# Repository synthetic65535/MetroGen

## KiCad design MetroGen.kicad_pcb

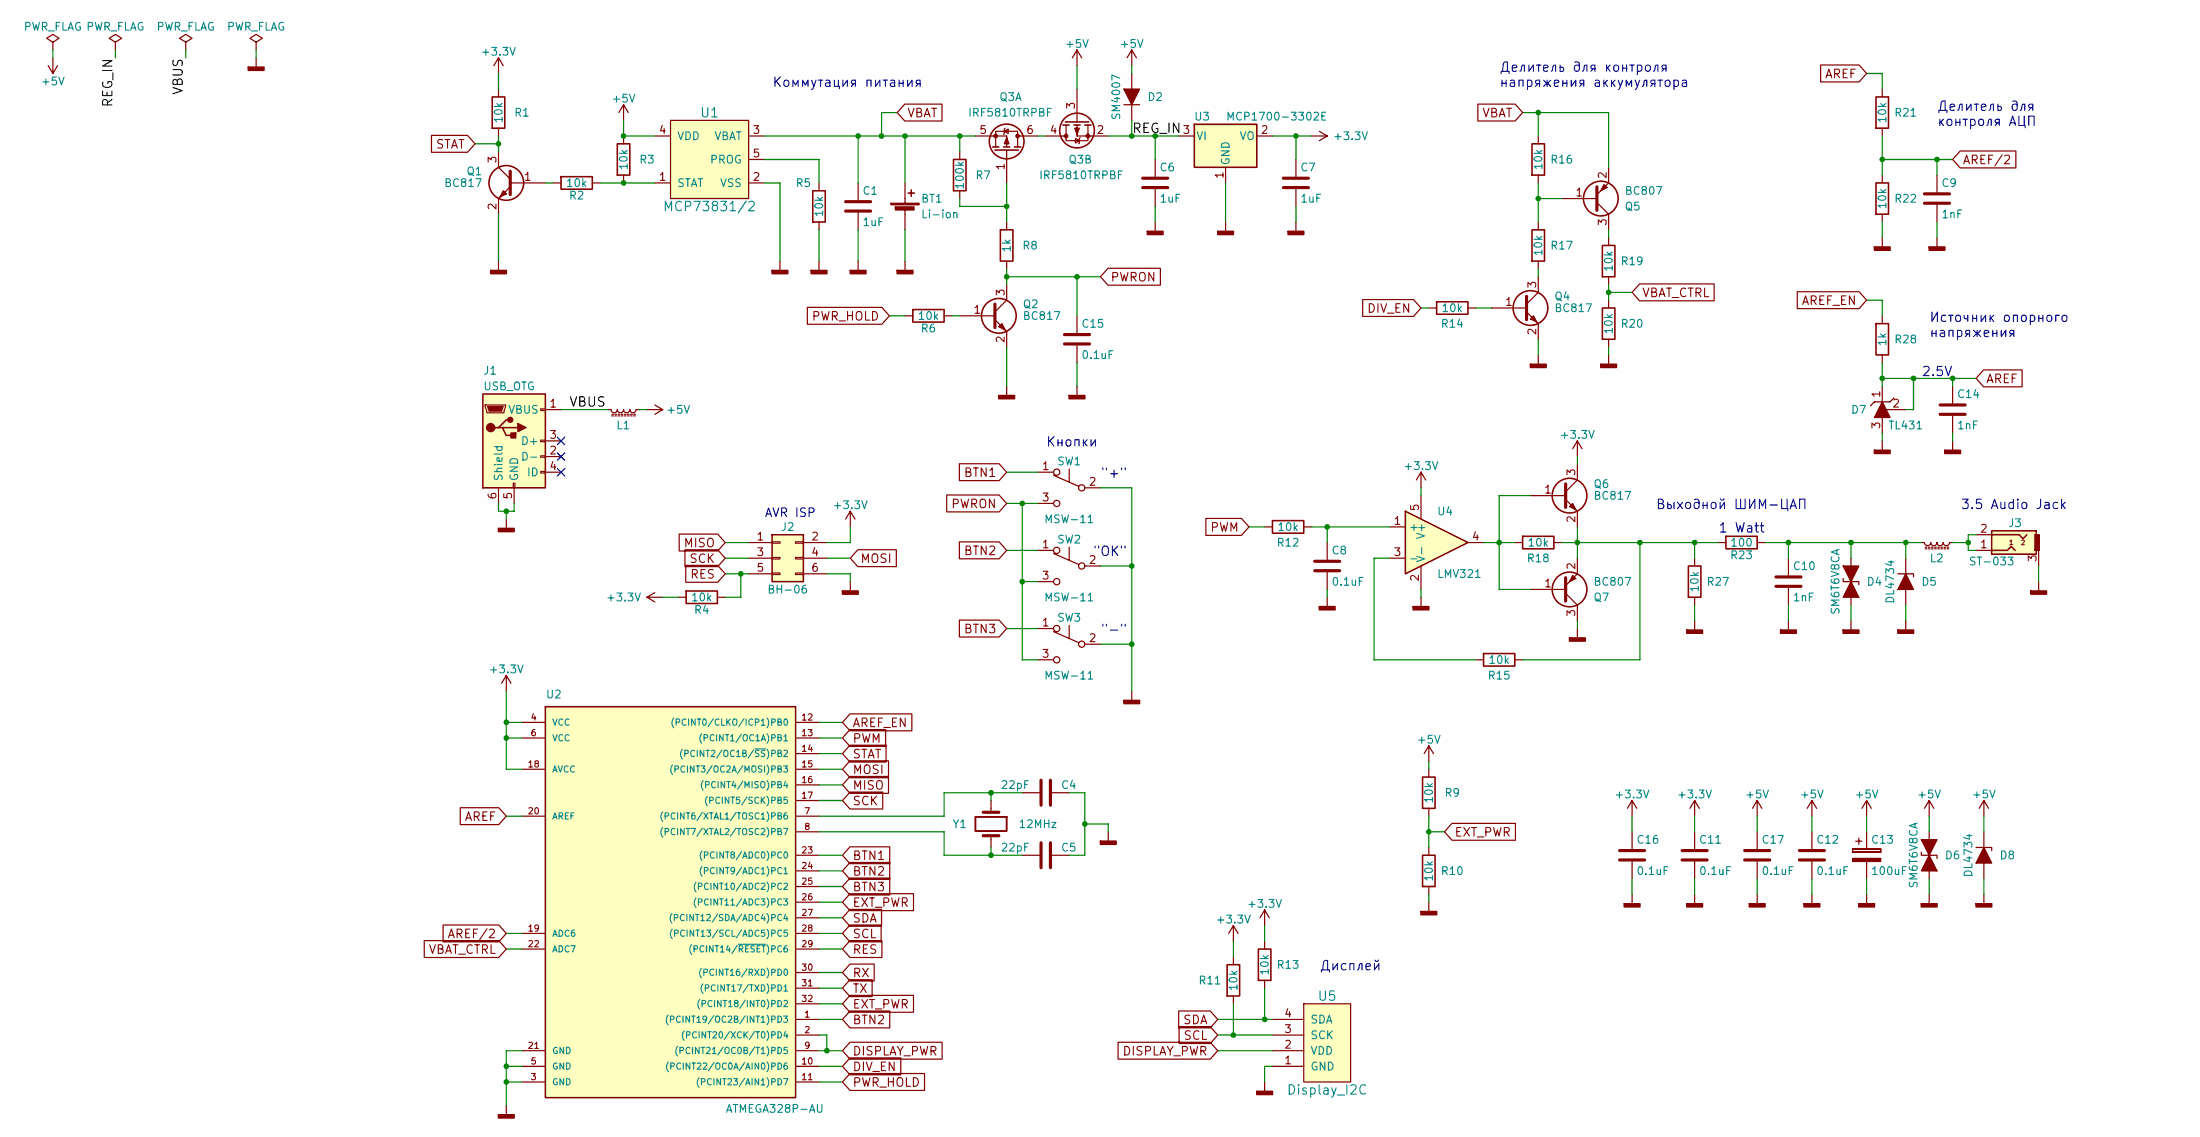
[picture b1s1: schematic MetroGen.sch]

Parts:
BT1: Li-ion; Case_Adaptive_for_18650-3
C1, C6, C7: 1uF; C_0805_HandSoldering
C4, C5: 22pF; C_0805_HandSoldering
C8, C11, C12, C15, C16, C17: 0.1uF; C_0805_HandSoldering
C9, C10, C14: 1nF; C_0805_HandSoldering
C13: 100uF; CP_Tantalum_Case-D_EIA-7343-31_Hand
D2: SM4007; D_MELF_Handsoldering
D4, D6: SM6T6V8CA; D_SMB_Handsoldering
D5, D8: DL4734; D_MELF_Handsoldering
D7: TL431; SOT-23_Handsoldering
J1: USB_OTG; USB_Mini-B
J2: BH-06; AVR_ISP
J3: ST-033; Audio_Jack_3.5
L1, L2: BLM21PG331SN1D; L_0805_HandSoldering
Q1, Q2, Q4, Q6: BC817; SOT-23_Handsoldering
Q3: IRF5810TRPBF; SOT-23-6_HandSoldering
Q5, Q7: BC807; SOT-23_Handsoldering
R1, R2, R3, R4, R5, R6, R9, R10, R11, R12, R13, R14, R15, R16, R17, R18, R19, R20, R21, R22, R27: 10k; R_0805_HandSoldering
R7: 100k; R_0805_HandSoldering
R8, R28: 1k; R_0805_HandSoldering
R23: 100; R_Axial_DIN0414_L11.9mm_D4.5mm_P15.24mm_Horizontal
SW1, SW2, SW3: MSW-11; SM5-00N-115
U1: MCP73831/2; SOT-23-5_HandSoldering
U2: ATMEGA328P-AU; TQFP-32_7x7mm_Pitch0.8mm
U3: MCP1700-3302E; SOT-23_Handsoldering
U4: LMV321; SOT-23-5_HandSoldering
U5: Display_I2C; Display_SSD1306
Y1: 12MHz; Crystal_HC49-4H_Vertical

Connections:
+3V3: C7.1, C11.1, C16.1, J2.2, Q6.3 (C), R1.1, R4.2, R11.1, R13.1, U2.4 (VCC), U2.6 (VCC), U2.18 (AVCC), U3.2 (VO), U4.5 (V+)
+5V: C12.1, C13.1, C17.1, D2.2 (A), D6.1 (A1), D8.1 (K), L1.1, Q3.3 (G), R3.1, R9.1, U1.4 (VDD)
/REG_IN: C6.1, D2.1 (K), Q3.2 (S), U3.3 (VI)
/VBUS: J1.1 (VBUS), L1.2
AREF: C14.1, D7.1 (K), D7.2 (REF), R21.1, R28.1, U2.20 (AREF)
AREF/2: C9.1, R21.2, R22.1, U2.19 (ADC6)
AREF_EN: R28.2, U2.12 ((PCINT0/CLKO/ICP1)PB0)
BTN1: SW1.1 (A), U2.23 ((PCINT8/ADC0)PC0)
BTN2: SW2.1 (A), U2.1 ((PCINT19/OC2B/INT1)PD3), U2.24 ((PCINT9/ADC1)PC1)
BTN3: SW3.1 (A), U2.25 ((PCINT10/ADC2)PC2)
DISPLAY_PWR: U2.2 ((PCINT20/XCK/T0)PD4), U2.9 ((PCINT21/OC0B/T1)PD5), U5.2 (VDD)
DIV_EN: R14.2, U2.10 ((PCINT22/OC0A/AIN0)PD6)
EXT_PWR: R9.2, R10.1, U2.26 ((PCINT11/ADC3)PC3), U2.32 ((PCINT18/INT0)PD2)
GNDD: BT1.2 (-), C1.2, C4.2, C5.2, C6.2, C7.2, C8.2, C9.2, C10.2, C11.2, C12.2, C13.2, C14.2, C15.2, C16.2, C17.2, D4.2 (A2), D5.2 (A), D6.2 (A2), D7.3 (A), D8.2 (A), J1.5 (GND), J1.6 (Shield), J2.6, J3.3, Q1.2 (E), Q2.2 (E), Q4.2 (E), Q7.3 (C), R5.2, R10.2, R20.2, R22.2, R27.2, SW1.2 (B), SW2.2 (B), SW3.2 (B), U1.2 (VSS), U2.3 (GND), U2.5 (GND), U2.21 (GND), U3.1 (GND), U4.2 (V-), U5.1 (GND)
MISO: J2.1, U2.16 ((PCINT4/MISO)PB4)
MOSI: J2.4, U2.15 ((PCINT3/OC2A/MOSI)PB3)
unnamed: C4.1, U2.7 ((PCINT6/XTAL1/TOSC1)PB6), Y1.1
unnamed: C5.1, U2.8 ((PCINT7/XTAL2/TOSC2)PB7), Y1.2
unnamed: C8.1, R12.1, U4.1 (+)
unnamed: C10.1, D4.1 (A1), D5.1 (K), L2.2, R23.1
unnamed: J3.1, J3.2, L2.1
unnamed: Q1.1 (B), R2.2
unnamed: Q2.1 (B), R6.1
unnamed: Q3.1 (G), R7.2, R8.2
unnamed: Q3.4 (D), Q3.6 (D)
unnamed: Q4.1 (B), R14.1
unnamed: Q4.3 (C), R17.2
unnamed: Q5.1 (B), R16.2, R17.1
unnamed: Q5.3 (C), R19.1
unnamed: Q6.1 (B), Q7.1 (B), R18.2, U4.4
unnamed: Q6.2 (E), Q7.2 (E), R15.1, R18.1, R23.2, R27.1
unnamed: R2.1, R3.2, U1.1 (STAT)
unnamed: R5.1, U1.5 (PROG)
unnamed: R15.2, U4.3 (-)
PWM: R12.2, U2.13 ((PCINT1/OC1A)PB1)
PWRON: C15.1, Q2.3 (C), R8.1, SW1.3 (C), SW2.3 (C), SW3.3 (C)
PWR_HOLD: R6.2, U2.11 ((PCINT23/AIN1)PD7)
RES: J2.5, R4.1, U2.29 ((PCINT14/~RESET~)PC6)
RX: U2.30 ((PCINT16/RXD)PD0)
SCK: J2.3, U2.17 ((PCINT5/SCK)PB5)
SCL: R11.2, U2.28 ((PCINT13/SCL/ADC5)PC5), U5.3 (SCK)
SDA: R13.2, U2.27 ((PCINT12/SDA/ADC4)PC4), U5.4 (SDA)
STAT: Q1.3 (C), R1.2, U2.14 ((PCINT2/OC1B/~SS~)PB2)
TX: U2.31 ((PCINT17/TXD)PD1)
VBAT: BT1.1 (+), C1.1, Q3.5 (S), Q5.2 (E), R7.1, R16.1, U1.3 (VBAT)
VBAT_CTRL: R19.2, R20.1, U2.22 (ADC7)

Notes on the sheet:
AVR ISP
1 Watt
3.5 Audio Jack
2.5V
"+"
"OK"
"-"
Коммутация питания
Кнопки
Делитель для контроля напряжения аккумулятора
Делитель для контроля АЦП
Источник опорного напряжения
Выходной ШИМ-ЦАП
Дисплей

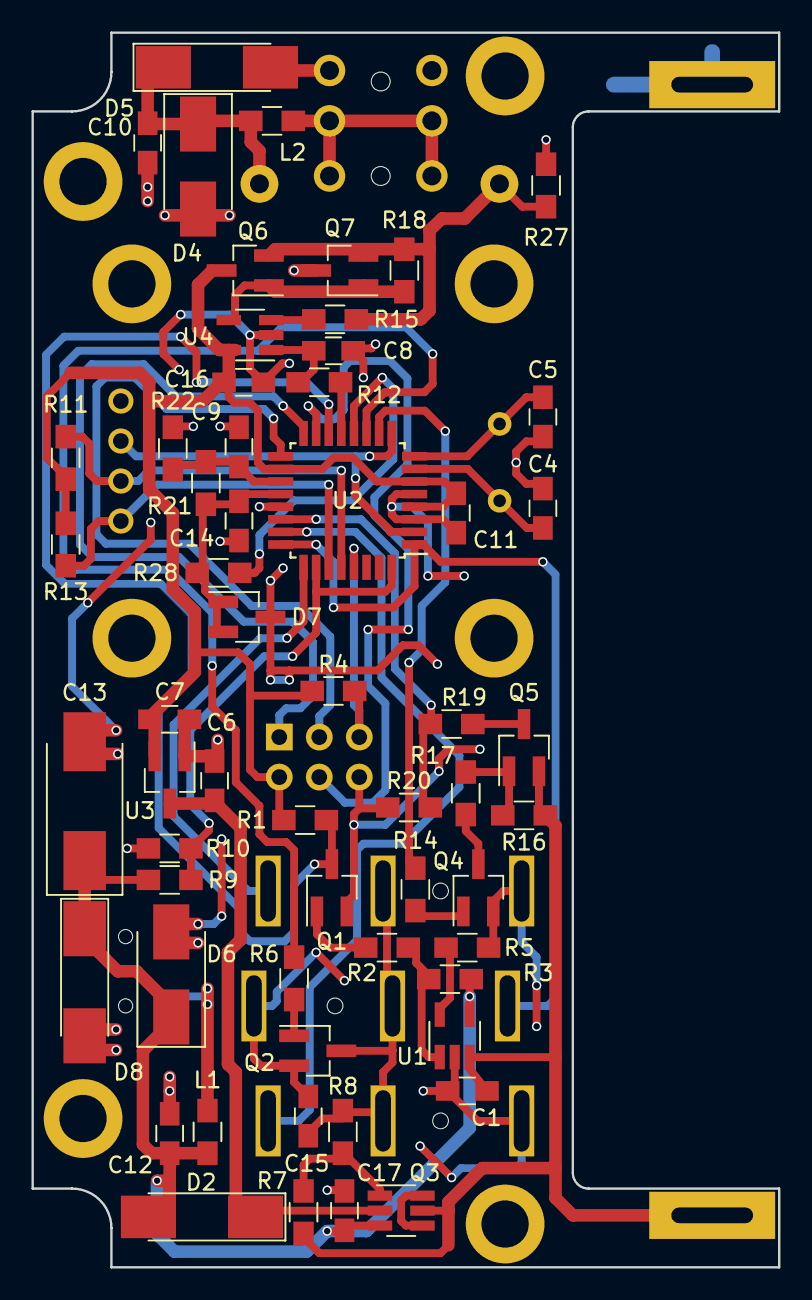
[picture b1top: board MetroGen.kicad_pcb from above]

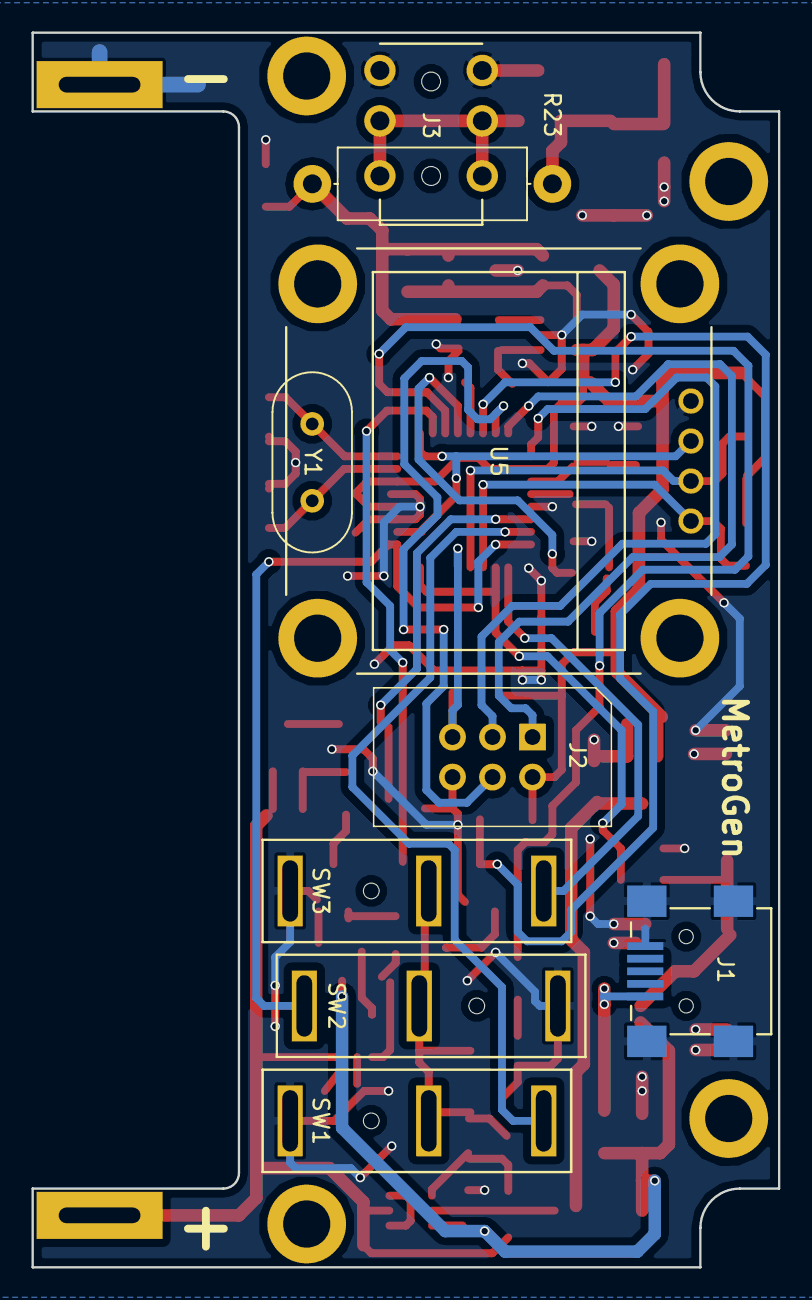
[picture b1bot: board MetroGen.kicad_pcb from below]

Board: 2 copper layers, 47.4 x 78.4 mm, 68 parts (9 on the bottom side), 44 nets.
